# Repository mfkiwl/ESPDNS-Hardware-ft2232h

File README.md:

# ESPDNS-Hardware

Open-source DNS filter, similar to Pi-Hole, based around the ESP32. 
Designed to be usable by people without the experience necessary to setup a Raspberry-pi.

This repository contains the KiCad projects for the full product and the programmer boards.

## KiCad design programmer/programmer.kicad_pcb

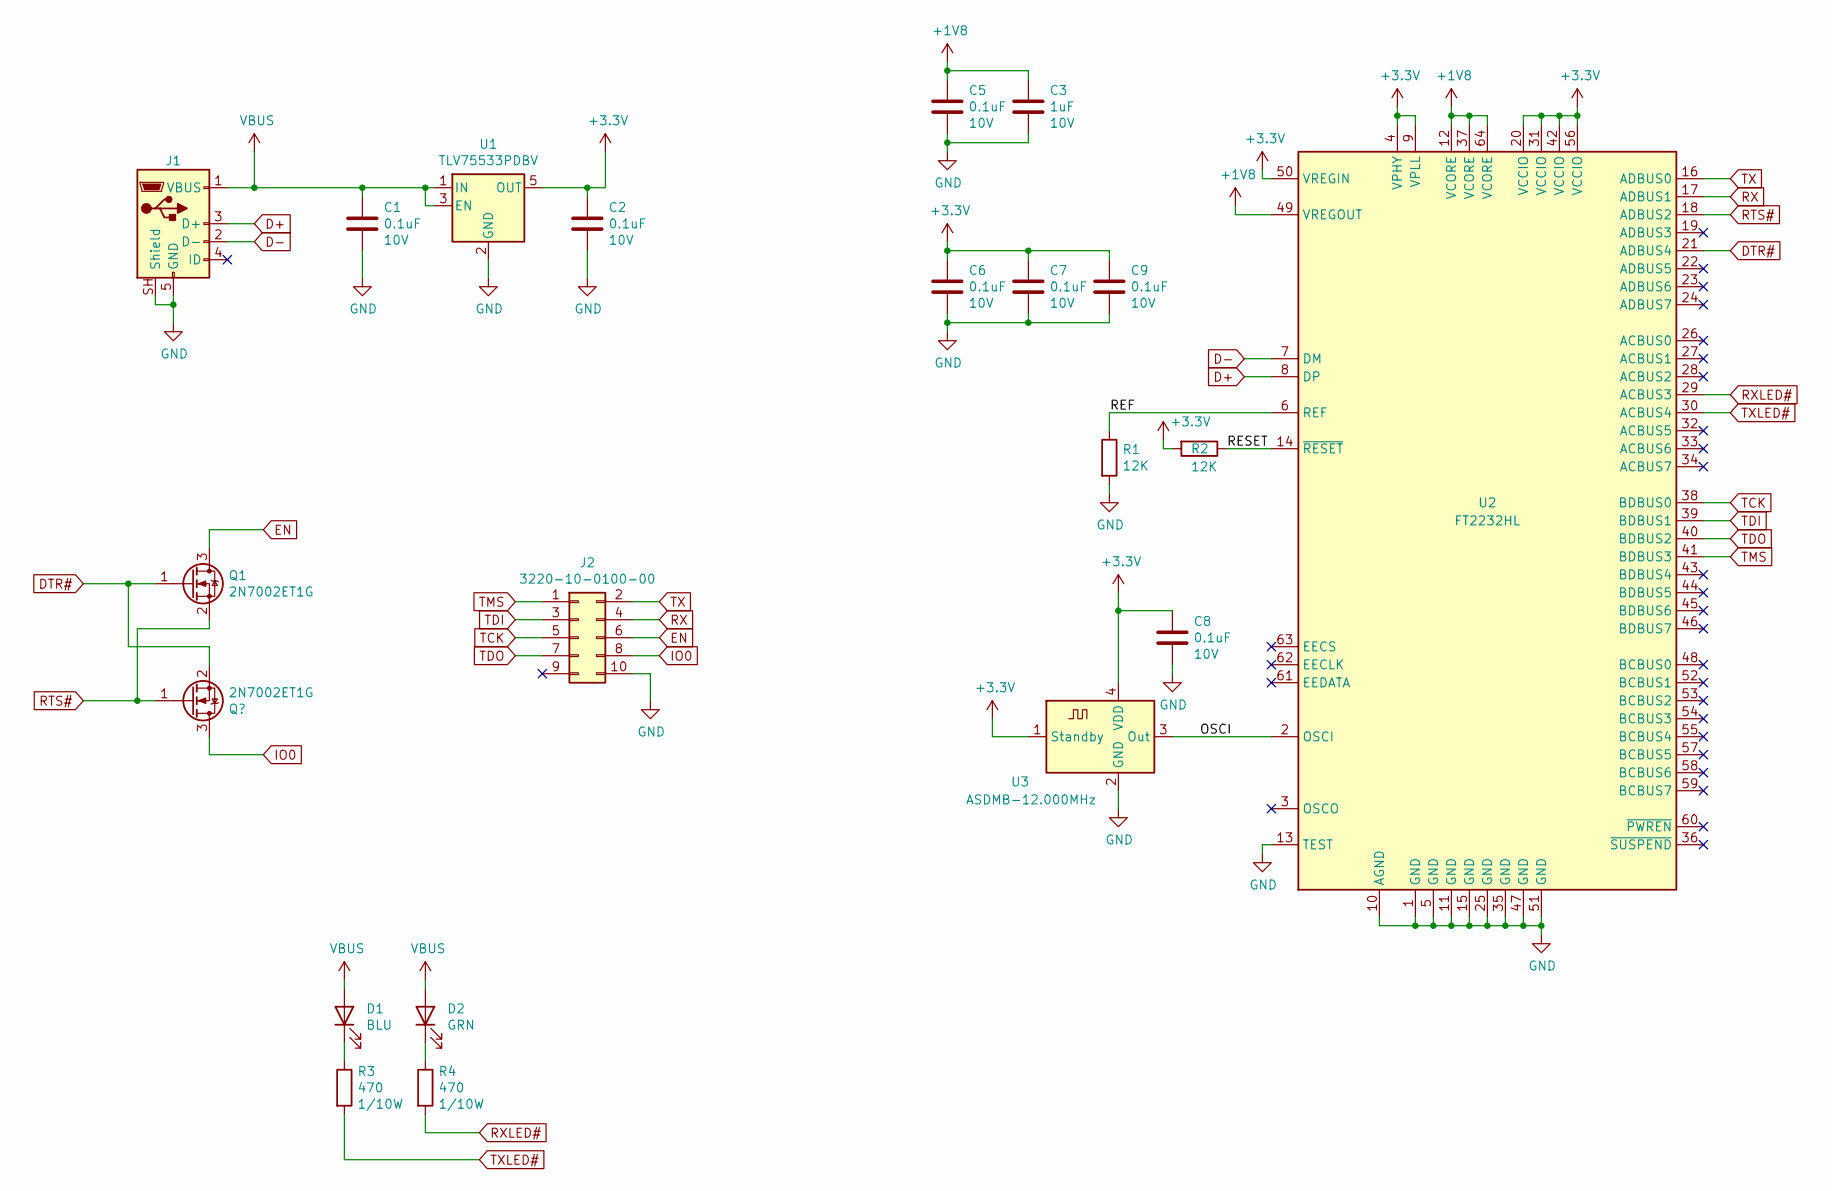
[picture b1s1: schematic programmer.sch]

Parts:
C1, C2, C5, C6, C7, C8, C9: 0.1uF; C_0603_1608Metric; Rating 10V
C3: 1uF; C_0603_1608Metric; Rating 10V
D1: BLU; LED_0603_1608Metric; Digikey Part Number 732-4966-1-ND
D2: GRN; LED_0603_1608Metric; Digikey Part Number 732-4971-1-ND
J1: 10118192-0001LF; AMPHENOL_10118192-0001LF; Digikey Part Number 1175-1627-ND
J2: 3220-10-0100-00; CNC_3220-10-0100-00; Digikey Part Number 1175-1627-ND
Q1: 2N7002ET1G; SOT-23; Digikey Part Number 2N7002ET1GOSCT-ND
R1, R2: 12K; R_0603_1608Metric
R3, R4: 470; R_0603_1608Metric; Rating 1/10W
U1: TLV75533PDBV; SOT-23-5; Digikey Part Number 296-50411-1-ND
U2: FT2232HL; LQFP-64_10x10mm_P0.5mm; Digikey Part Number 768-1347-ND
U3: ASDMB-12.000MHz; Oscillator_SMD_Abracon_ASDMB-4Pin_2.5x2.0mm; Digikey Part Number 535-11180-1-ND

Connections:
+1V8: C3.1, C5.1, U2.12 (VCORE), U2.37 (VCORE), U2.49 (VREGOUT), U2.64 (VCORE)
+3V3: C2.1, C6.1, C7.1, C8.1, C9.1, R2.2, U1.5 (OUT), U2.4 (VPHY), U2.9 (VPLL), U2.20 (VCCIO), U2.31 (VCCIO), U2.42 (VCCIO), U2.50 (VREGIN), U2.56 (VCCIO), U3.1 (Standby), U3.4 (VDD)
/OSCI: U2.2 (OSCI), U3.3 (Out)
/REF: R1.1, U2.6 (REF)
/RESET: R2.1, U2.14 (~RESET)
D+: J1.3 (D+), U2.8 (DP)
D-: J1.2 (D-), U2.7 (DM)
DTR#: Q1.1 (G), U2.21 (ADBUS4); also elsewhere on the board
EN: J2.6, Q1.3 (D)
GND: C1.2, C2.2, C3.2, C5.2, C6.2, C7.2, C8.2, C9.2, J1.5 (GND), J1.SH (Shield), J2.10, R1.2, U1.2 (GND), U2.1 (GND), U2.5 (GND), U2.10 (AGND), U2.11 (GND), U2.13 (TEST), U2.15 (GND), U2.25 (GND), U2.35 (GND), U2.47 (GND), U2.51 (GND), U3.2 (GND)
IO0: J2.8; also elsewhere on the board
unnamed: D1.1 (K), R3.1
unnamed: D2.1 (K), R4.1
RTS#: Q1.2 (S), U2.18 (ADBUS2); also elsewhere on the board
RX: J2.4, U2.17 (ADBUS1)
RXLED#: R4.2, U2.29 (ACBUS3)
TCK: J2.5, U2.38 (BDBUS0)
TDI: J2.3, U2.39 (BDBUS1)
TDO: J2.7, U2.40 (BDBUS2)
TMS: J2.1, U2.41 (BDBUS3)
TX: J2.2, U2.16 (ADBUS0)
TXLED#: R3.2, U2.30 (ACBUS4)
VBUS: C1.1, D1.2 (A), D2.2 (A), J1.1 (VBUS), U1.1 (IN), U1.3 (EN)

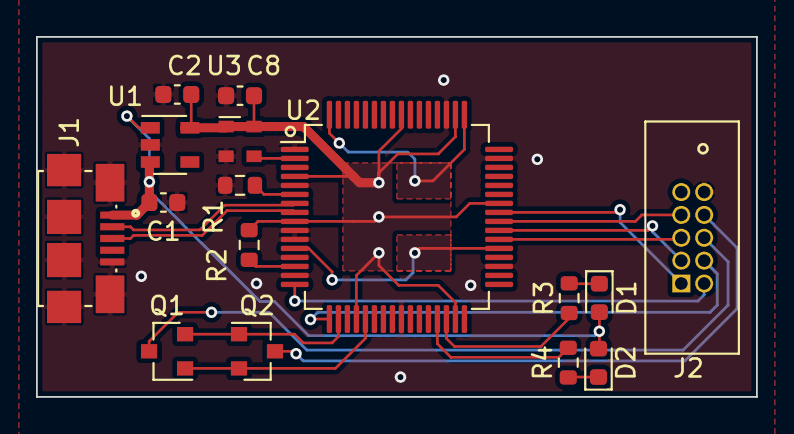
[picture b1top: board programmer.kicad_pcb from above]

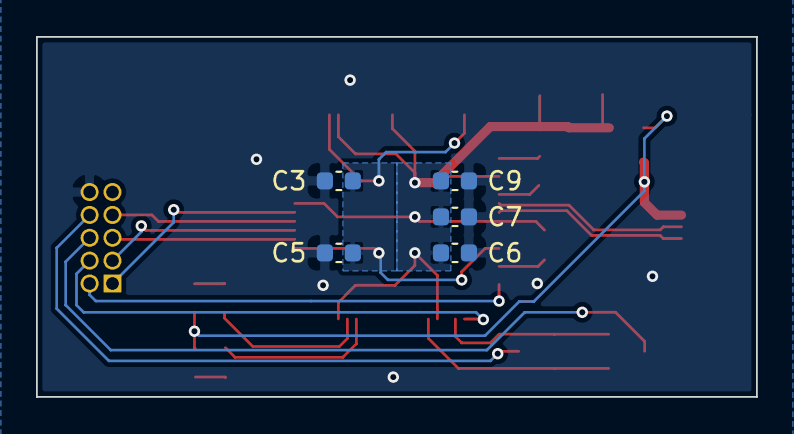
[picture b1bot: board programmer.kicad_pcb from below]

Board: 2 copper layers, 40.0 x 20.0 mm, 21 parts (5 on the bottom side), 23 nets.

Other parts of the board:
Q2: Q_NMOS_GSD; SOT-23

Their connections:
DTR#: Q2.2; also elsewhere on the board
IO0: Q2.3; also elsewhere on the board
RTS#: Q2.1; also elsewhere on the board

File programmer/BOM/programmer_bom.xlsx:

Component | Description | Part | References | Value | Footprint | Quantity Per PCB | Datasheet | Rating | LCSC Part Number | Digikey Part Number | Alternate Datasheet | LCSC Alternate
1 | Unpolarized capacitor | C | C1 C2 C5 C6 C7 C8 C9 | 0.1uF | C_0603_1608Metric | 7 | ~ | 10V | C14663 | ~ | ~ | ~
2 | Unpolarized capacitor | C | C3 | 1uF | C_0603_1608Metric | 1 | ~ | 10V | C15849 | ~ | ~ | ~
3 | Light emitting diode | LED | D1 | BLU | LED_0603_1608Metric | 1 | https://www.we-online.de/katalog/datasheet/150060BS75000.pdf | ~ | C72041 | 732-4966-1-ND | https://datasheet.lcsc.com/szlcsc/Everlight-Elec-19-217-BHC-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 | 19-217/BHC-ZL1M2RY/3T
4 | Light emitting diode | LED | D2 | GRN | LED_0603_1608Metric | 1 | https://www.we-online.de/katalog/datasheet/150060GS75000.pdf | ~ | C72043 | 732-4971-1-ND | https://datasheet.lcsc.com/szlcsc/Everlight-Elec-19-217-GHC-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 | 19-217/GHC-YR1S2/3T
5 | USB Micro Type B connector | USB_B_Micro | J1 | 10118192-0001LF | AMPHENOL_10118192-0001LF | 1 | https://www.amphenol-icc.com/media/wysiwyg/files/drawing/101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 | ~ | ~ | 1175-1627-ND | ~ | ~
6 | Generic connector, double row, 02x05, odd/even pin numbering scheme (row 1 odd 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 | Conn_02x05_Odd_Even | J2 | 3220-10-0100-00 | CNC_3220-10-0100-00 | 1 | http://www.cnctech.us/pdfs/3220-XX-0100-00_.pdf | ~ | ~ | 1175-1627-ND | ~ | ~
7 | N-MOSFET transistor, gate/source/drain | Q_NMOS_GSD | Q1 Q2 | 2N7002ET1G | SOT-23 | 2 | https://www.onsemi.com/pub/Collateral/2N7002E-D.PDF | ~ | C8545 | 2N7002ET1GOSCT-ND | https://datasheet.lcsc.com/szlcsc/Changjiang-Electronics-Tec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 | 2N7002
8 | Resistor | R | R3 R4 | 470 | R_0603_1608Metric | 2 | ~ | 1/10W | C23179 | ~ | ~ | ~
9 | Resistor | R | R1 R2 | 12K | R_0603_1608Metric | 2 | ~ | ~ | C22790 | ~ | ~ | ~
10 | 1.8-3.3V SMD Ultra Miniature Crystal Clock Oscillator, Abracon | ASDMB-xxxMHz | U3 | ASDMB-12.000MHz | Oscillator_SMD_Abracon_ASDMB-4Pin_2.5x2.0mm | 1 | https://abracon.com/Oscillators/ASDMB.pdf | ~ | C90619 | 535-11180-1-ND | https://datasheet.lcsc.com/szlcsc/Yangxing-Tech-O252012MEDH4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 | O252012MEDH4MI
11 | Hi Speed Double Channel USB UART/FIFO, LQFP-64 | FT2232HL | U2 | FT2232HL | LQFP-64_10x10mm_P0.5mm | 1 | https://www.ftdichip.com/Support/Documents/DataSheets/ICs/DS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 | ~ | C27882 | 768-1347-ND | ~ | ~
12 | 500mA Low Dropout Voltage Regulator, Fixed Output 3.3V, SOT-23-5 | TLV75533PDBV | U1 | TLV75533PDBV | SOT-23-5 | 1 | http://www.ti.com/lit/ds/symlink/tlv755p.pdf | ~ | C404027 | 296-50411-1-ND | ~ | ~
Component Groups: | 12
Component Count: | 21
Fitted Components: | 21
Number of PCBs: | 1
Total components: | 21
Schematic Version:
Schematic Date:
PCB Variant: | default
BoM Date: | 44167.400347222225
Schematic Source: | programmer.sch
KiCad Version: | Eeschema (5.1.7)-1

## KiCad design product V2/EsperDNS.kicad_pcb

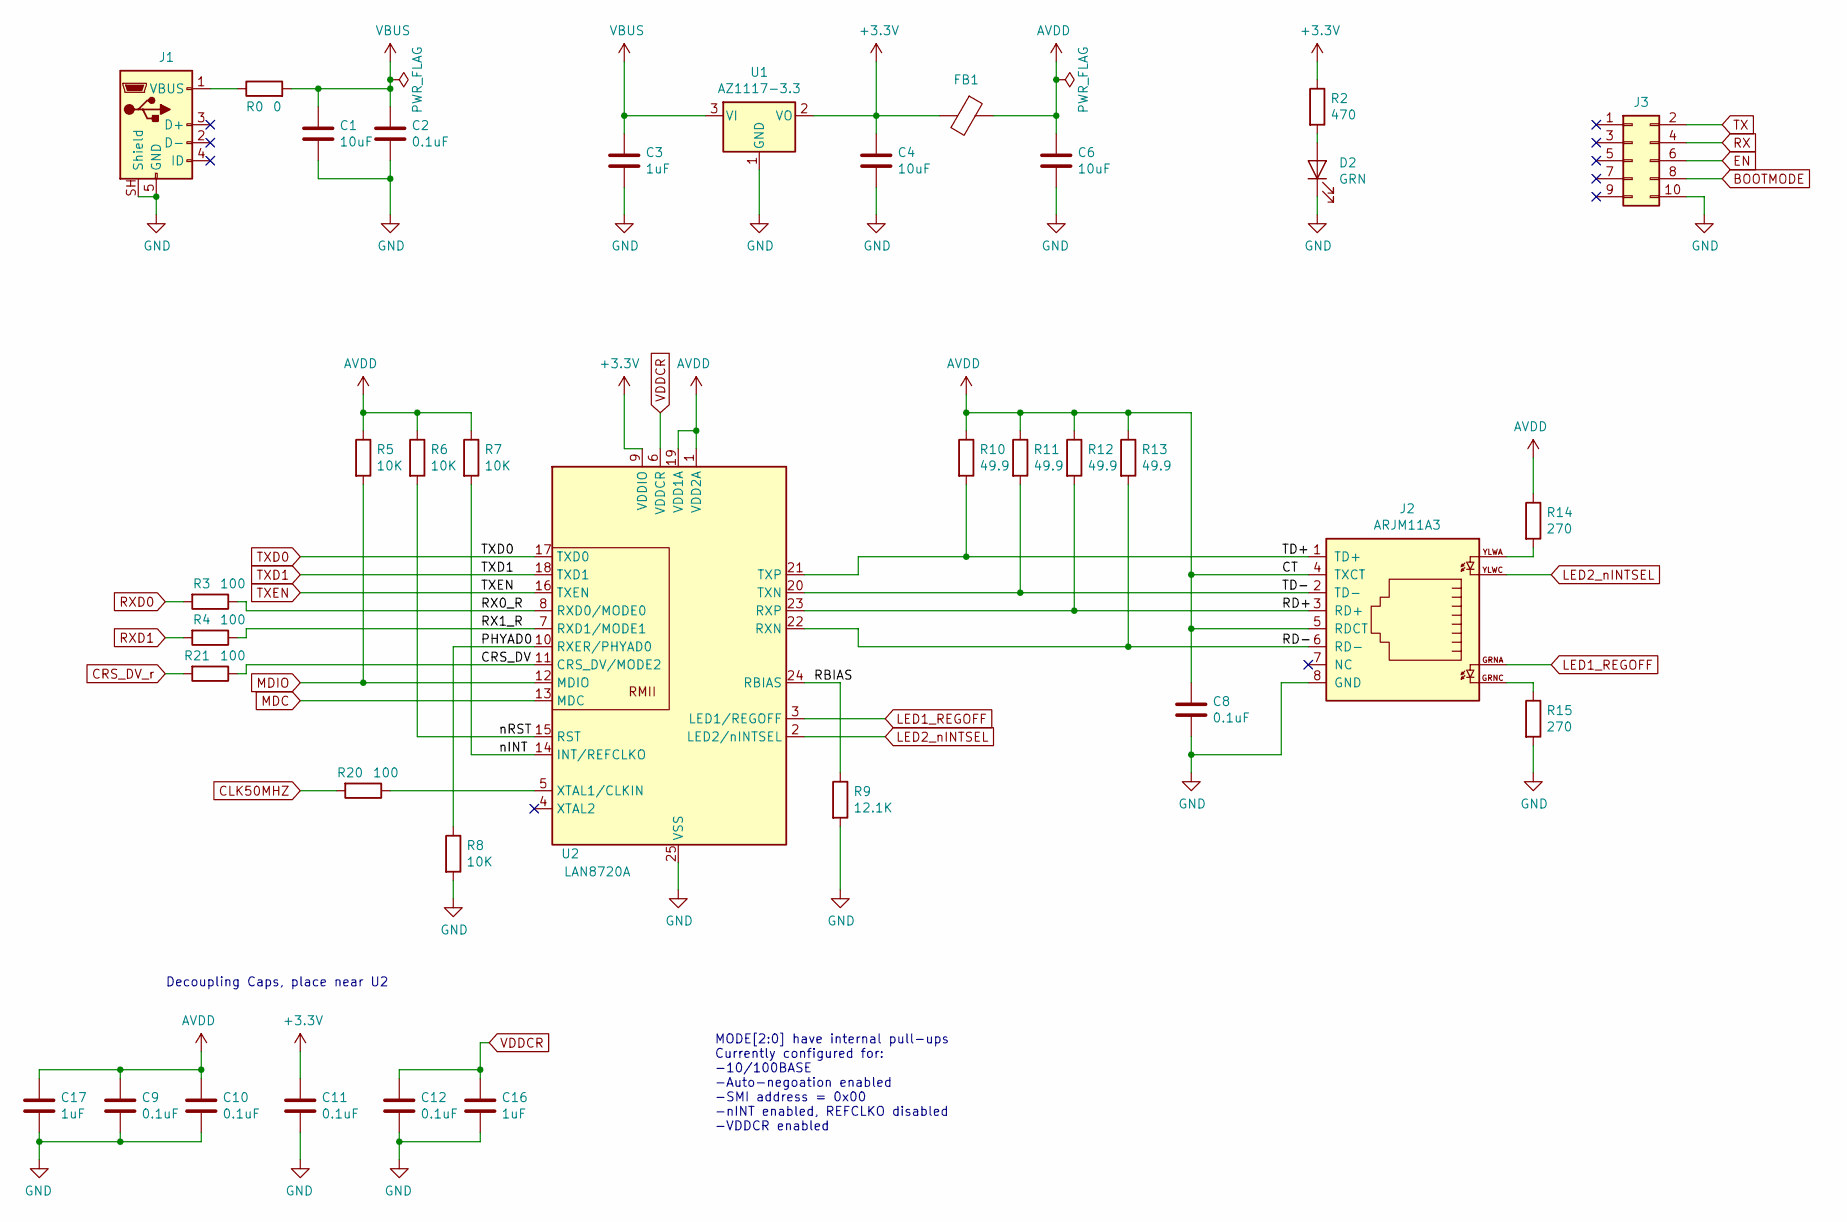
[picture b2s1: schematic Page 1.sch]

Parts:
C1: 10uF; C_0603_1608Metric; LCSC Part Number C77044
C2, C8, C9, C10, C11, C12: 0.1uF; C_0603_1608Metric; LCSC Part Number C24452
C3, C16, C17: 1uF; C_0603_1608Metric; LCSC Part Number C1525
C4, C6: 10uF; C_0603_1608Metric; LCSC Part Number C99226
D2: GRN; D_0603_1608Metric; LCSC Part Number C125094
FB1: Ferrite_Bead; L_0603_1608Metric; LCSC Part Number C82850
J1: 10118192-0001LF; USB_Micro_B_Female_10118192; LCSC Part Number C132564
J2: ARJM11A3; ARJM11A3-009-AB-ER2-T
J3: Conn_02x05_Odd_Even; PinSocket_2x05_P2.54mm_Vertical
R0: 0; R_0603_1608Metric; LCSC Part Number C95177
R2: 470; R_0603_1608Metric; LCSC Part Number C114433
R3, R4, R20, R21: 100; R_0603_1608Metric; LCSC Part Number C105588
R5, R6, R7, R8: 10K; R_0603_1608Metric; LCSC Part Number C99198
R9: 12.1K; R_0603_1608Metric; LCSC Part Number C123417
R10, R11, R12, R13: 49.9; R_0603_1608Metric; LCSC Part Number C114625
R14, R15: 270; R_0603_1608Metric; LCSC Part Number C137641
U1: AZ1117-3.3; SOT-223; LCSC Part Number C92517
U2: LAN8720A; QFN-24-1EP_4x4mm_P0.5mm_EP2.6x2.6mm; LCSC Part Number C45223

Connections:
+3V3: C4.1, C11.1, FB1.2, R2.1, U1.2 (VO), U2.9 (VDDIO); also elsewhere on the board
/Page 1/CRS_DV: R21.1, U2.11 (CRS_DV/MODE2)
/Page 1/PHYAD0: R8.1, U2.10 (RXER/PHYAD0)
/Page 1/RBIAS: R9.1, U2.24 (RBIAS)
/Page 1/RD+: J2.3 (RD+), R12.2, U2.23 (RXP)
/Page 1/RD-: J2.6 (RD-), R13.2, U2.22 (RXN)
/Page 1/RX0_R: R3.1, U2.8 (RXD0/MODE0)
/Page 1/RX1_R: R4.1, U2.7 (RXD1/MODE1)
/Page 1/TD+: J2.1 (TD+), R10.2, U2.21 (TXP)
/Page 1/TD-: J2.2 (TD-), R11.2, U2.20 (TXN)
/Page 1/nINT: R7.2, U2.14 (INT/REFCLKO)
/Page 1/nRST: R6.2, U2.15 (RST)
AVDD: C6.1, C8.1, C9.1, C10.1, C17.1, FB1.1, J2.4 (TXCT), J2.5 (RDCT), R5.1, R6.1, R7.1, R10.1, R11.1, R12.1, R13.1, R14.1, U2.1 (VDD2A), U2.19 (VDD1A)
BOOTMODE: J3.8; also elsewhere on the board
CLK50MHZ: R20.2; also elsewhere on the board
CRS_DV_r: R21.2; also elsewhere on the board
EN: J3.6; also elsewhere on the board
GND: C1.2, C2.2, C3.2, C4.2, C6.2, C8.2, C9.2, C10.2, C11.2, C12.2, C16.2, C17.2, D2.1 (K), J1.5 (GND), J1.SH (Shield), J2.8 (GND), J3.10, R8.2, R9.2, R15.2, U1.1 (GND), U2.25 (VSS); also elsewhere on the board
LED1_REGOFF: J2.GRNA, U2.3 (LED1/REGOFF)
LED2_nINTSEL: J2.YLWC, U2.2 (LED2/nINTSEL)
MDC: U2.13 (MDC); also elsewhere on the board
MDIO: R5.2, U2.12 (MDIO); also elsewhere on the board
unnamed: D2.2 (A), R2.2
unnamed: J1.1 (VBUS), R0.1
unnamed: J2.GRNC, R15.1
unnamed: J2.YLWA, R14.2
unnamed: R20.1, U2.5 (XTAL1/CLKIN)
RX: J3.4; also elsewhere on the board
RXD0: R3.2; also elsewhere on the board
RXD1: R4.2; also elsewhere on the board
TX: J3.2; also elsewhere on the board
TXD0: U2.17 (TXD0); also elsewhere on the board
TXD1: U2.18 (TXD1); also elsewhere on the board
TXEN: U2.16 (TXEN); also elsewhere on the board
VBUS: C1.1, C2.1, C3.1, R0.2, U1.3 (VI); also elsewhere on the board
VDDCR: C12.1, C16.1, U2.6 (VDDCR)

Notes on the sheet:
MODE[2:0] have internal pull-ups Currently configured for: -10/100BASE -Auto-negoation enabled -SMI address = 0x00 -nINT enabled, REFCLKO disabled -VDDCR enabled
Decoupling Caps, place near U2

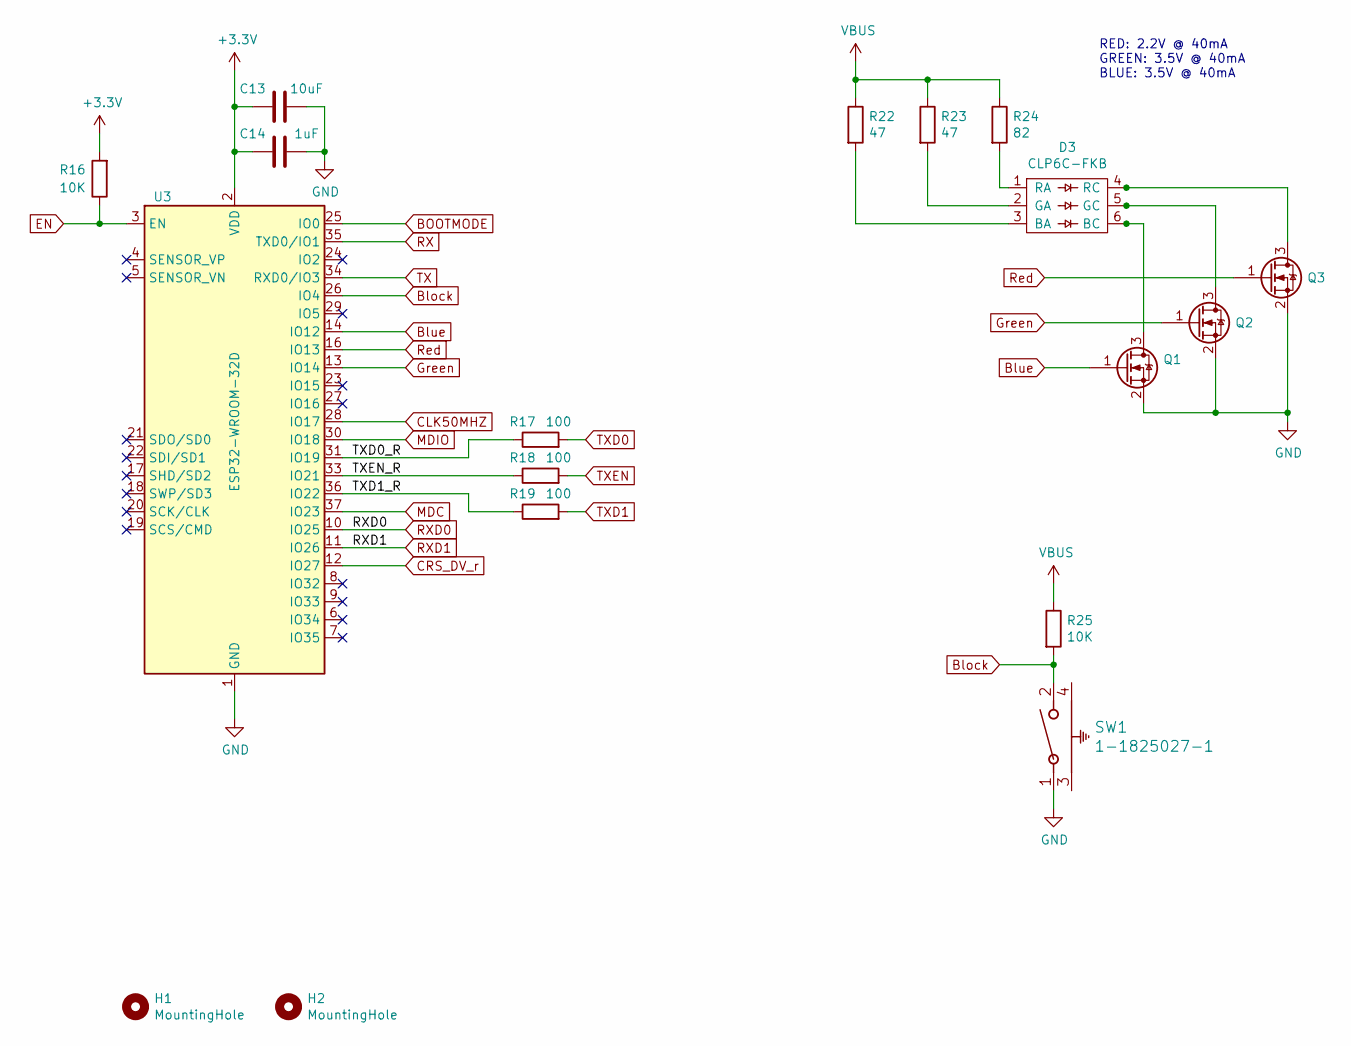
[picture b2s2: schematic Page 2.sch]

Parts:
C13: 10uF; C_0603_1608Metric; LCSC Part Number C77044
C14: 1uF; C_0603_1608Metric; LCSC Part Number C1525
D3: CLP6C-FKB
H1, H2: MountingHole; MountingHole_2.2mm_M2_Pad
Q1, Q2, Q3: Q_NMOS_GSD; SOT-23-3
R16: 10K; R_0603_1608Metric; LCSC Part Number C99198
R17, R18, R19: 100; R_0603_1608Metric; LCSC Part Number C105588
R22, R23: 47; R_0603_1608Metric
R24: 82; R_0603_1608Metric
R25: 10K; R_0603_1608Metric
SW1: 1-1825027-1
U3: ESP32-WROOM-32D; ESP32-WROOM-32; LCSC Part Number C95209

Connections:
+3V3: C13.2, C14.2, R16.2, U3.2 (VDD); also elsewhere on the board
/Page 2/TXD0_R: R17.1, U3.31 (IO19)
/Page 2/TXD1_R: R19.1, U3.36 (IO22)
/Page 2/TXEN_R: R18.1, U3.33 (IO21)
BOOTMODE: U3.25 (IO0); also elsewhere on the board
Block: R25.2, SW1.2, U3.26 (IO4)
Blue: Q1.1 (G), U3.14 (IO12)
CLK50MHZ: U3.28 (IO17); also elsewhere on the board
CRS_DV_r: U3.12 (IO27); also elsewhere on the board
EN: R16.1, U3.3 (EN); also elsewhere on the board
GND: C13.1, C14.1, Q1.2 (S), Q2.2 (S), Q3.2 (S), SW1.1, U3.1 (GND), U3.15 (GND), U3.38 (GND), U3.39 (GND); also elsewhere on the board
Green: Q2.1 (G), U3.13 (IO14)
MDC: U3.37 (IO23); also elsewhere on the board
MDIO: U3.30 (IO18); also elsewhere on the board
unnamed: D3.1 (RA), R24.2
unnamed: D3.2 (GA), R23.2
unnamed: D3.3 (BA), R22.2
unnamed: D3.4 (RC), Q3.3 (D)
unnamed: D3.5 (GC), Q2.3 (D)
unnamed: D3.6 (BC), Q1.3 (D)
RX: U3.35 (TXD0/IO1); also elsewhere on the board
RXD0: U3.10 (IO25); also elsewhere on the board
RXD1: U3.11 (IO26); also elsewhere on the board
Red: Q3.1 (G), U3.16 (IO13)
TX: U3.34 (RXD0/IO3); also elsewhere on the board
TXD0: R17.2; also elsewhere on the board
TXD1: R19.2; also elsewhere on the board
TXEN: R18.2; also elsewhere on the board
VBUS: R22.1, R23.1, R24.1, R25.1; also elsewhere on the board

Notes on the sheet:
RED: 2.2V @ 40mA GREEN: 3.5V @ 40mA BLUE: 3.5V @ 40mA

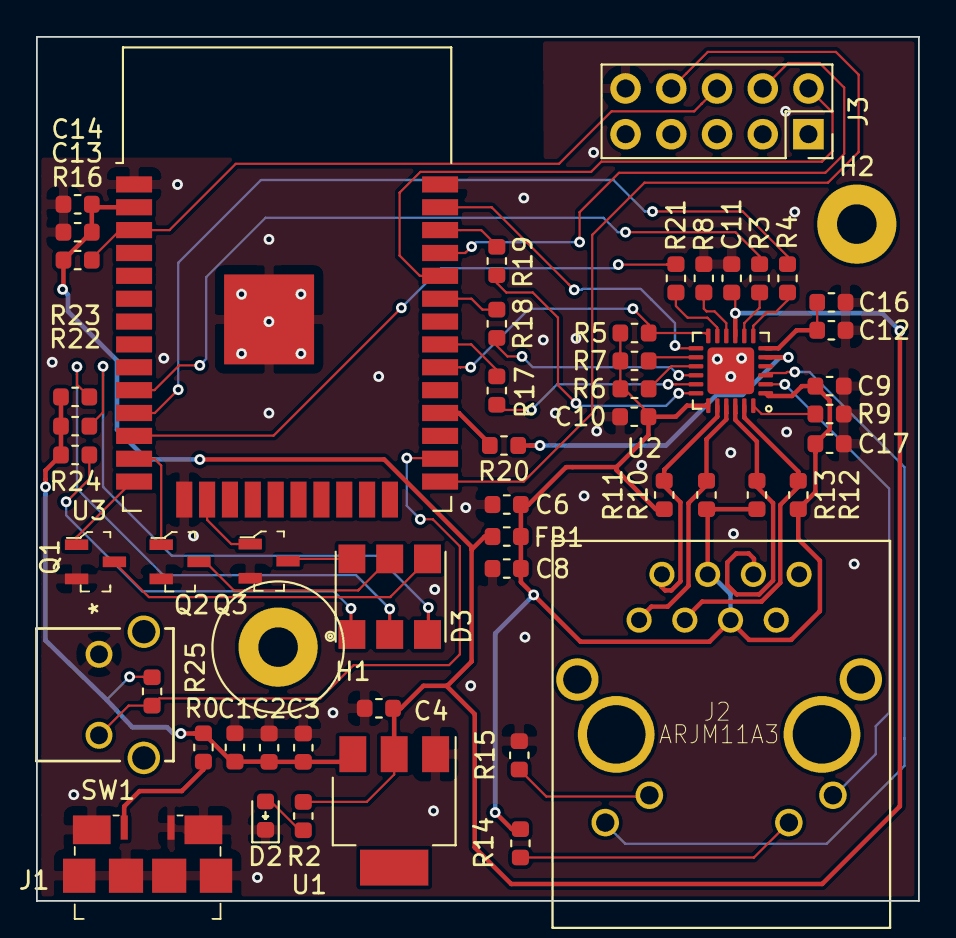
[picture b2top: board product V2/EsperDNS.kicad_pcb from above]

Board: 2 copper layers, 49.0 x 48.0 mm, 54 parts (0 on the bottom side), 49 nets.

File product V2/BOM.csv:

"Source:","C:\Users\v-zamorr.REDMOND\ESPDNS-Hardware\product V2\EsperDNS.sch"
"Date:","9/3/2020 10:42:57 AM"
"Tool:","Eeschema (5.1.4)-1"
"Generator:","C:\Program Files\KiCad\bin\scripting\plugins/bom_csv_grouped_by_value.py"
"Component Count:","54"

"Individual Components:"

"Item","Qty","Reference(s)","Value","LibPart","Footprint","Datasheet","LCSC Part Number"
"","","C1","10uF","Device:C","Capacitor_SMD:C_0603_1608Metric","~","C77044"
"","","C2","0.1uF","Device:C","Capacitor_SMD:C_0603_1608Metric","~","C24452"
"","","C3","1uF","Device:C","Capacitor_SMD:C_0603_1608Metric","~","C1525"
"","","C4","4.7uF","Device:C","Capacitor_SMD:C_0603_1608Metric","~","C99226"
"","","C6","4.7uF","Device:C","Capacitor_SMD:C_0603_1608Metric","~","C99226"
"","","C8","0.1uF","Device:C","Capacitor_SMD:C_0603_1608Metric","~","C24452"
"","","C9","0.1uF","Device:C","Capacitor_SMD:C_0603_1608Metric","~","C24452"
"","","C10","0.1uF","Device:C","Capacitor_SMD:C_0603_1608Metric","~","C24452"
"","","C11","0.1uF","Device:C","Capacitor_SMD:C_0603_1608Metric","~","C24452"
"","","C12","0.1uF","Device:C","Capacitor_SMD:C_0603_1608Metric","~","C24452"
"","","C13","10uF","Device:C","Capacitor_SMD:C_0603_1608Metric","~","C77044"
"","","C14","1uF","Device:C","Capacitor_SMD:C_0603_1608Metric","~","C1525"
"","","C16","1uF","Device:C","Capacitor_SMD:C_0603_1608Metric","~","C1525"
"","","C17","1uF","Device:C","Capacitor_SMD:C_0603_1608Metric","~","C1525"
"","","D2","GRN","Device:LED","Diode_SMD:D_0603_1608Metric","~","C125094"
"","","D3","CLP6C-FKB","My_Symbols:CLP6C-FKB","My Footprints:CLP6C-FKB","",""
"","","FB1","Ferrite_Bead","Device:Ferrite_Bead","Inductor_SMD:L_0603_1608Metric","~","C82850"
"","","H1","MountingHole","Mechanical:MountingHole","MountingHole:MountingHole_2.2mm_M2_Pad","~",""
"","","H2","MountingHole","Mechanical:MountingHole","MountingHole:MountingHole_2.2mm_M2_Pad","~",""
"","","J1","10118192-0001LF","EsperDNS-rescue:10118192-0001LF-Symbols","digikey-footprints:USB_Micro_B_Female_10118192","~","C132564"
"","","J2","ARJM11A3","EsperDNS-rescue:ARJM11A3-ARJM11A3-009-AB-ER2-T","My Footprints:ARJM11A3-009-AB-ER2-T","",""
"","","J3","Conn_02x05_Odd_Even","Connector_Generic:Conn_02x05_Odd_Even","Connector_PinSocket_2.54mm:PinSocket_2x05_P2.54mm_Vertical","~",""
"","","Q1","Q_NMOS_GSD","Device:Q_NMOS_GSD","digikey-footprints:SOT-23-3","~",""
"","","Q2","Q_NMOS_GSD","Device:Q_NMOS_GSD","digikey-footprints:SOT-23-3","~",""
"","","Q3","Q_NMOS_GSD","Device:Q_NMOS_GSD","digikey-footprints:SOT-23-3","~",""
"","","R0","0","Device:R","Resistor_SMD:R_0603_1608Metric","~","C95177"
"","","R2","470","Device:R","Resistor_SMD:R_0603_1608Metric","~","C114433"
"","","R3","100","Device:R","Resistor_SMD:R_0603_1608Metric","~","C105588"
"","","R4","100","Device:R","Resistor_SMD:R_0603_1608Metric","~","C105588"
"","","R5","10K","Device:R","Resistor_SMD:R_0603_1608Metric","~","C99198"
"","","R6","10K","Device:R","Resistor_SMD:R_0603_1608Metric","~","C99198"
"","","R7","10K","Device:R","Resistor_SMD:R_0603_1608Metric","~","C99198"
"","","R8","10K","Device:R","Resistor_SMD:R_0603_1608Metric","~","C99198"
"","","R9","12.1K","Device:R","Resistor_SMD:R_0603_1608Metric","~","C123417"
"","","R10","49.9","Device:R","Resistor_SMD:R_0603_1608Metric","~","C114625"
"","","R11","49.9","Device:R","Resistor_SMD:R_0603_1608Metric","~","C114625"
"","","R12","49.9","Device:R","Resistor_SMD:R_0603_1608Metric","~","C114625"
"","","R13","49.9","Device:R","Resistor_SMD:R_0603_1608Metric","~","C114625"
"","","R14","270","Device:R","Resistor_SMD:R_0603_1608Metric","~","C137641"
"","","R15","270","Device:R","Resistor_SMD:R_0603_1608Metric","~","C137641"
"","","R16","10K","Device:R","Resistor_SMD:R_0603_1608Metric","~","C99198"
"","","R17","100","Device:R","Resistor_SMD:R_0603_1608Metric","~","C105588"
"","","R18","100","Device:R","Resistor_SMD:R_0603_1608Metric","~","C105588"
"","","R19","100","Device:R","Resistor_SMD:R_0603_1608Metric","~","C105588"
"","","R20","100","Device:R","Resistor_SMD:R_0603_1608Metric","~","C105588"
"","","R21","100","Device:R","Resistor_SMD:R_0603_1608Metric","~","C105588"
"","","R22","R","Device:R","Resistor_SMD:R_0603_1608Metric","~",""
"","","R23","R","Device:R","Resistor_SMD:R_0603_1608Metric","~",""
"","","R24","R","Device:R","Resistor_SMD:R_0603_1608Metric","~",""
"","","R25","10K","Device:R","Resistor_SMD:R_0603_1608Metric","~",""
"","","SW1","1-1825027-1","1-1825027-1:1-1825027-1","1-1825027-1:1-1825027-1","",""
"","","U1","AZ1117-3.3","Regulator_Linear:AZ1117-3.3","Package_TO_SOT_SMD:SOT-223","https://www.diodes.com/assets/Datasheets/AZ1117.pdf","C92517"
"","","U2","LAN8720A","Interface_Ethernet:LAN8720A","Package_DFN_QFN:QFN-24-1EP_4x4mm_P0.5mm_EP2.6x2.6mm","http://ww1.microchip.com/downloads/en/DeviceDoc/8720a.pdf","C45223"
"","","U3","ESP32-WROOM-32D","EsperDNS-rescue:ESP32-WROOM-32D-RF_Module","RF_Module:ESP32-WROOM-32","https://www.espressif.com/sites/default/files/documentation/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"," 	C95209"



"Collated Components:"

"Item","Qty","Reference(s)","Value","LibPart","Footprint","Datasheet","LCSC Part Number"
"1","2","C1, C13","10uF","Device:C","Capacitor_SMD:C_0603_1608Metric","~","C77044"
"2","6","C2, C8, C9, C10, C11, C12","0.1uF","Device:C","Capacitor_SMD:C_0603_1608Metric","~","C24452"
"3","4","C3, C14, C16, C17","1uF","Device:C","Capacitor_SMD:C_0603_1608Metric","~","C1525"
"4","2","C4, C6","4.7uF","Device:C","Capacitor_SMD:C_0603_1608Metric","~","C99226"
"5","1","D2","GRN","Device:LED","Diode_SMD:D_0603_1608Metric","~","C125094"
"6","1","D3","CLP6C-FKB","My_Symbols:CLP6C-FKB","My Footprints:CLP6C-FKB","",""
"7","1","FB1","Ferrite_Bead","Device:Ferrite_Bead","Inductor_SMD:L_0603_1608Metric","~","C82850"
"8","2","H1, H2","MountingHole","Mechanical:MountingHole","MountingHole:MountingHole_2.2mm_M2_Pad","~",""
"9","1","J1","10118192-0001LF","EsperDNS-rescue:10118192-0001LF-Symbols","digikey-footprints:USB_Micro_B_Female_10118192","~","C132564"
"10","1","J2","ARJM11A3","EsperDNS-rescue:ARJM11A3-ARJM11A3-009-AB-ER2-T","My Footprints:ARJM11A3-009-AB-ER2-T","",""
"11","1","J3","Conn_02x05_Odd_Even","Connector_Generic:Conn_02x05_Odd_Even","Connector_PinSocket_2.54mm:PinSocket_2x05_P2.54mm_Vertical","~",""
"12","3","Q1, Q2, Q3","Q_NMOS_GSD","Device:Q_NMOS_GSD","digikey-footprints:SOT-23-3","~",""
"13","1","R0","0","Device:R","Resistor_SMD:R_0603_1608Metric","~","C95177"
"14","1","R2","470","Device:R","Resistor_SMD:R_0603_1608Metric","~","C114433"
"15","7","R3, R4, R17, R18, R19, R20, R21","100","Device:R","Resistor_SMD:R_0603_1608Metric","~","C105588"
"16","6","R5, R6, R7, R8, R16, R25","10K","Device:R","Resistor_SMD:R_0603_1608Metric","~","C99198"
"17","1","R9","12.1K","Device:R","Resistor_SMD:R_0603_1608Metric","~","C123417"
"18","4","R10, R11, R12, R13","49.9","Device:R","Resistor_SMD:R_0603_1608Metric","~","C114625"
"19","2","R14, R15","270","Device:R","Resistor_SMD:R_0603_1608Metric","~","C137641"
"20","3","R22, R23, R24","R","Device:R","Resistor_SMD:R_0603_1608Metric","~",""
"21","1","SW1","1-1825027-1","1-1825027-1:1-1825027-1","1-1825027-1:1-1825027-1","",""
"22","1","U1","AZ1117-3.3","Regulator_Linear:AZ1117-3.3","Package_TO_SOT_SMD:SOT-223","https://www.diodes.com/assets/Datasheets/AZ1117.pdf","C92517"
"23","1","U2","LAN8720A","Interface_Ethernet:LAN8720A","Package_DFN_QFN:QFN-24-1EP_4x4mm_P0.5mm_EP2.6x2.6mm","http://ww1.microchip.com/downloads/en/DeviceDoc/8720a.pdf","C45223"
"24","1","U3","ESP32-WROOM-32D","EsperDNS-rescue:ESP32-WROOM-32D-RF_Module","RF_Module:ESP32-WROOM-32","https://www.espressif.com/sites/default/files/documentation/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"," 	C95209"

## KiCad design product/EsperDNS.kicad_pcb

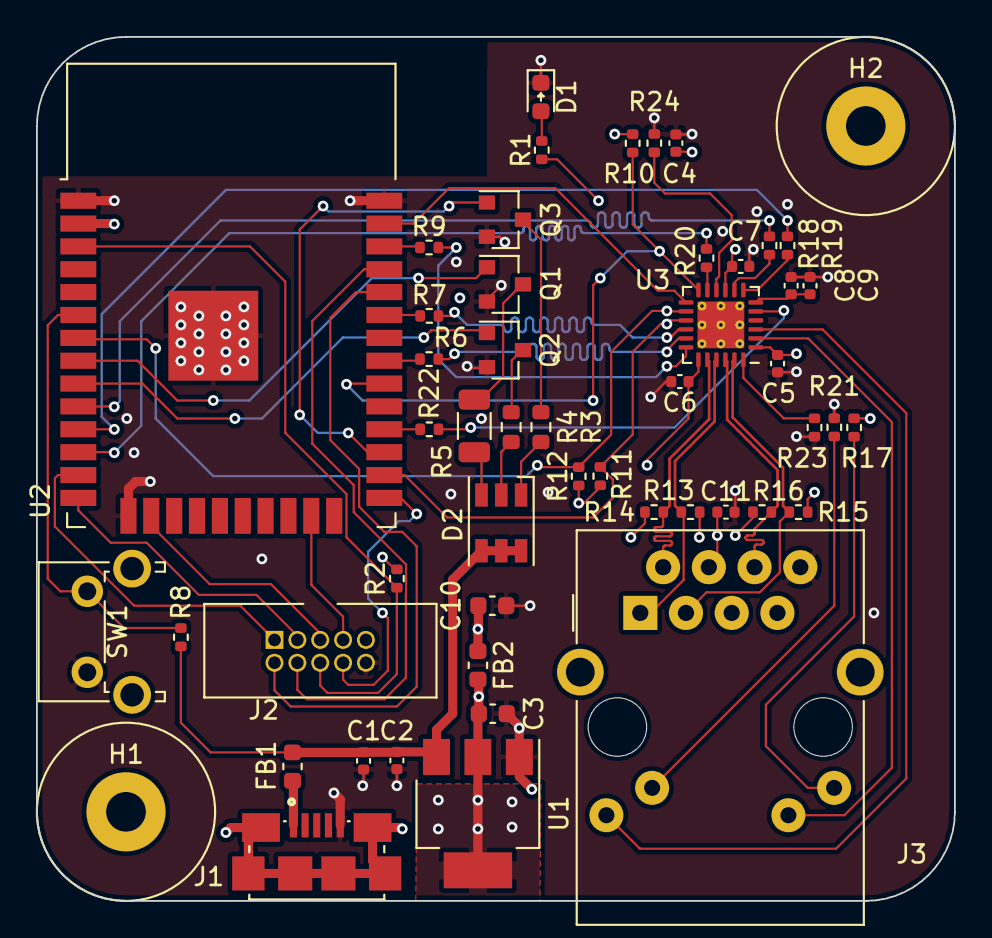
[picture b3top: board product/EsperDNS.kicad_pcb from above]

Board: 4 copper layers, 51.0 x 48.0 mm, 51 parts (0 on the bottom side), 54 nets.

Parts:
C1, C4, C9: 1uF; C_0402_1005Metric
C2, C5, C6, C7, C8, C11: 0.1uF; C_0402_1005Metric
C3, C10: 10uF; C_0603_1608Metric
D1: GRN; D_0603_1608Metric
D2: RS-3535MWAP; LED_RGB_PLCC-6
FB1, FB2: Ferrite_Bead; L_0603_1608Metric
H1, H2: MountingHole; MountingHole_2.2mm_M2_Pad
J1: 10118192-0001LF; AMPHENOL_10118192-0001LF
J2: Conn_02x05_Odd_Even; CNC_3220-10-0100-00
J3: RJ45_Amphenol_RJMG1BD3B8K1ANR
Q1, Q2, Q3: Q_NMOS_GSD; SOT-23
R1: 470; R_0402_1005Metric
R2, R8, R10, R11, R12, R24: 10K; R_0402_1005Metric
R3, R4: 47; R_0603_1608Metric
R5: 82; R_1206_3216Metric
R6, R7, R9, R13, R14, R15, R16, R18, R19, R20, R22: 49.9; R_0402_1005Metric
R17, R21: 270; R_0402_1005Metric
R23: 12.1K; R_0402_1005Metric
SW1: PTS645VH83-2 LFS; SW_Tactile_SPST_Angled_PTS645Vx83-2LFS
U1: AZ1117EH-3.3; SOT-223
U2: ESP32-WROOM-32D; ESP32-WROOM-32
U3: LAN8720A; QFN-24-1EP_4x4mm_P0.5mm_EP2.6x2.6mm_ThermalVias

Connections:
+3.3VA: C4.1, C5.1, C6.1, C10.1, C11.1, FB2.1, J3.R4, J3.R5, R10.1, R11.1, R12.1, R13.1, R14.1, R15.1, R16.1, R17.1, U3.1, U3.19
+3V3: C3.1, C7.1, FB2.2, R1.1, R2.2, U1.2, U1.4, U2.2, U3.9
/ESP32/CLK_R: R22.2, U2.28
/ESP32/TXD0_R: R6.1, U2.31
/ESP32/TXD1_R: R9.1, U2.36
/ESP32/TXEN_R: R7.1, U2.33
/Ethernet/CRS_DV_R: R20.1, U3.11
/Ethernet/LEDG_K: J3.L3, R21.1
/Ethernet/LEDY_A: J3.L1, R17.2
/Ethernet/PHYAD0: R24.1, U3.10
/Ethernet/RBIAS: R23.1, U3.24
/Ethernet/RD+: J3.R3, R15.2, U3.23
/Ethernet/RD-: J3.R6, R16.2, U3.22
/Ethernet/RX0_R: R18.1, U3.8
/Ethernet/RX1_R: R19.1, U3.7
/Ethernet/TD+: J3.R1, R13.2, U3.21
/Ethernet/TD-: J3.R2, R14.2, U3.20
Block: R8.2, SW1.2, U2.6
Blue: Q3.1, U2.27
CLK50MHZ: R22.1, U3.5
CRS_DV: R20.2, U2.12
EN: J2.6, R2.1, U2.3
Earth: H1.1, H2.1, J1.6, J3.13
GND: C1.2, C2.2, C3.2, C4.2, C5.2, C6.2, C7.2, C8.2, C9.2, C10.2, C11.2, D1.1, J1.5, J2.10, J3.R8, Q1.2, Q2.2, Q3.2, R21.2, R23.2, R24.2, SW1.1, U1.1, U2.1, U2.15, U2.38, U2.39, U3.25
Green: Q2.1, U2.9
IO0: J2.8, U2.25
LED1_REGOFF: J3.L4, U3.3
LED2_nINTSEL: J3.L2, U3.2
MDC: U2.37, U3.13
MDIO: R10.2, U2.30, U3.12
MTCK: J2.5, U2.16
MTDI: J2.3, U2.14
MTDO: J2.7, U2.23
MTMS: J2.1, U2.13
unnamed: D1.2, R1.2
unnamed: D2.1, R3.1
unnamed: D2.2, R4.1
unnamed: D2.3, R5.1
unnamed: FB1.2, J1.1
unnamed: Q1.3, R5.2
unnamed: Q2.3, R4.2
unnamed: Q3.3, R3.2
RX: J2.4, U2.35
RXD0: R18.2, U2.10
RXD1: R19.2, U2.11
Red: Q1.1, U2.8
TX: J2.2, U2.34
TXD0: R6.2, U3.17
TXD1: R9.2, U3.18
TXEN: R7.2, U3.16
VBUS: C1.1, C2.1, D2.4, D2.5, D2.6, FB1.1, R8.1, U1.3
VDDCR: C8.1, C9.1, U3.6
nINT: R12.2, U2.7, U3.14
nRST: R11.2, U2.26, U3.15

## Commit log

2019-12-05 First page added
2019-12-05 Second page finished
2019-12-05 Corrected mistakes, added refdes
2019-12-06 Started assigning footprints
2019-12-06 Assigning footprints
2019-12-06 Started laying out board
2019-12-06 Schematic changes
2019-12-09 Worked on board
2019-12-10 Finished first revision of board
2019-12-11 Stuff
2019-12-11 Started on programmer board
2019-12-11 Added first revision of programmer board
2019-12-14 Changed programmer parts to LCSC parts, added part numbers
2019-12-15 Added LCSC part numbers for product board
2019-12-15 Added .gitignore and added BOMs for programmer
2020-05-16 Swapped TX & RX on Product Board
2020-05-31 Moved connector and added silkscreen labels on product board
2020-06-18 Last commit before removing oscillator, currently boots and obtains IP address
2020-08-12 Removed oscillator, replaced with IO17
2020-08-14 First Draft Of New Form Factor
2020-08-27 Editted traces to improve signal intregrity
2020-08-28 Started adding LEDs and pushbuttons to board
2020-09-01 Added block button and RGB LED
2020-09-14 Added buttons and LEDs
2020-09-16 Added Picture to README
2020-11-09 Create ToDo
2020-11-12 Changed board outline and mounting to better fit inside enclosure
2020-12-02 Updated programmer to include jtag and dtr signals. Swapped FT230X for FT2232HL
2020-12-02 Finished version 2 of programmer, now with JTAG
2020-12-04 Finished layout
2020-12-04 Added LCSC part numbers, and tweaked a few part footprints
